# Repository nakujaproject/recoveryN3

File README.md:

# recoveryN3
Everything pertaining recovery system for N3 Rocket 2023

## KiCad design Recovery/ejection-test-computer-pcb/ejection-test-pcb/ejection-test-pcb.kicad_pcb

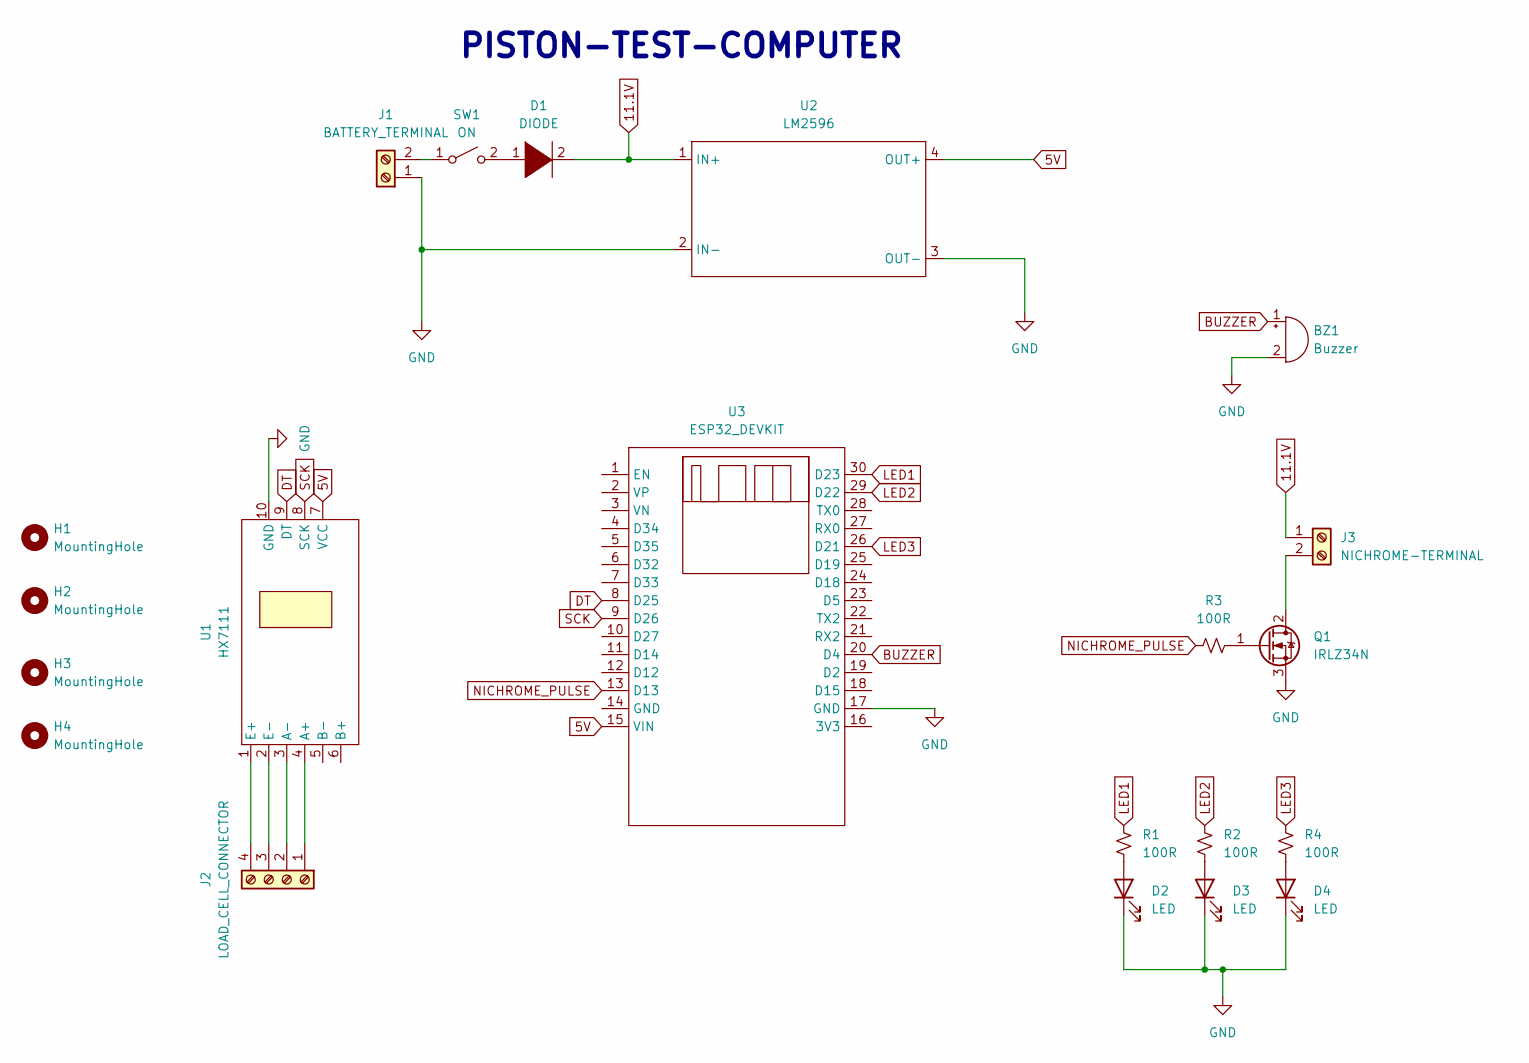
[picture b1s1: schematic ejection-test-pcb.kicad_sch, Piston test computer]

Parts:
BZ1: Buzzer; BUZZER
D1: DIODE; D_DO-35_SOD27_P10.16mm_Horizontal
D2, D3, D4: LED; LED_D5.0mm
H1, H2, H3, H4: MountingHole; MountingHole_3.2mm_M3
J1: BATTERY_TERMINAL; TerminalBlock_bornier-2_P5.08mm
J2: LOAD_CELL_CONNECTOR; TerminalBlock_bornier-4_P5.08mm
J3: NICHROME-TERMINAL; TerminalBlock_bornier-2_P5.08mm
Q1: IRLZ34N; TO-220-3_Vertical
R1, R2, R3, R4: 100R; R_Axial_DIN0207_L6.3mm_D2.5mm_P10.16mm_Horizontal
SW1: ON; KDC1-11-ROCKER-SWITCH
U1: HX7111; HX711
U2: LM2596; LM2596-BUCK-CONVERTER
U3: ESP32_DEVKIT

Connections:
5V: U1.7 (VCC), U2.4 (OUT+), U3.15 (VIN)
11.1V: D1.2 (A), J3.1, U2.1 (IN+)
BUZZER: BZ1.1 (-), U3.20 (D4)
DT: U1.9 (DT), U3.8 (D25)
GND: BZ1.2 (+), D2.1 (K), D3.1 (K), D4.1 (K), J1.1, Q1.3 (S), U1.10 (GND), U2.2 (IN-), U2.3 (OUT-), U3.17 (GND)
LED1: R1.1, U3.18 (D15), U3.30 (D23)
LED2: R2.1, U3.29 (D22)
LED3: R4.1, U3.26 (D21)
NICHROME_PULSE: R3.2, U3.13 (D13)
unnamed: D1.1 (K), SW1.2 (B)
unnamed: D2.2 (A), R1.2
unnamed: D3.2 (A), R2.2
unnamed: D4.2 (A), R4.2
unnamed: J1.2, SW1.1 (A)
unnamed: J2.1, U1.4 (A+)
unnamed: J2.2, U1.3 (A-)
unnamed: J2.3, U1.2 (E-)
unnamed: J2.4, U1.1 (E+)
unnamed: J3.2, Q1.2 (D)
unnamed: Q1.1 (G), R3.1
SCK: U1.8 (SCK), U3.9 (D26)

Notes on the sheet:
PISTON-TEST-COMPUTER

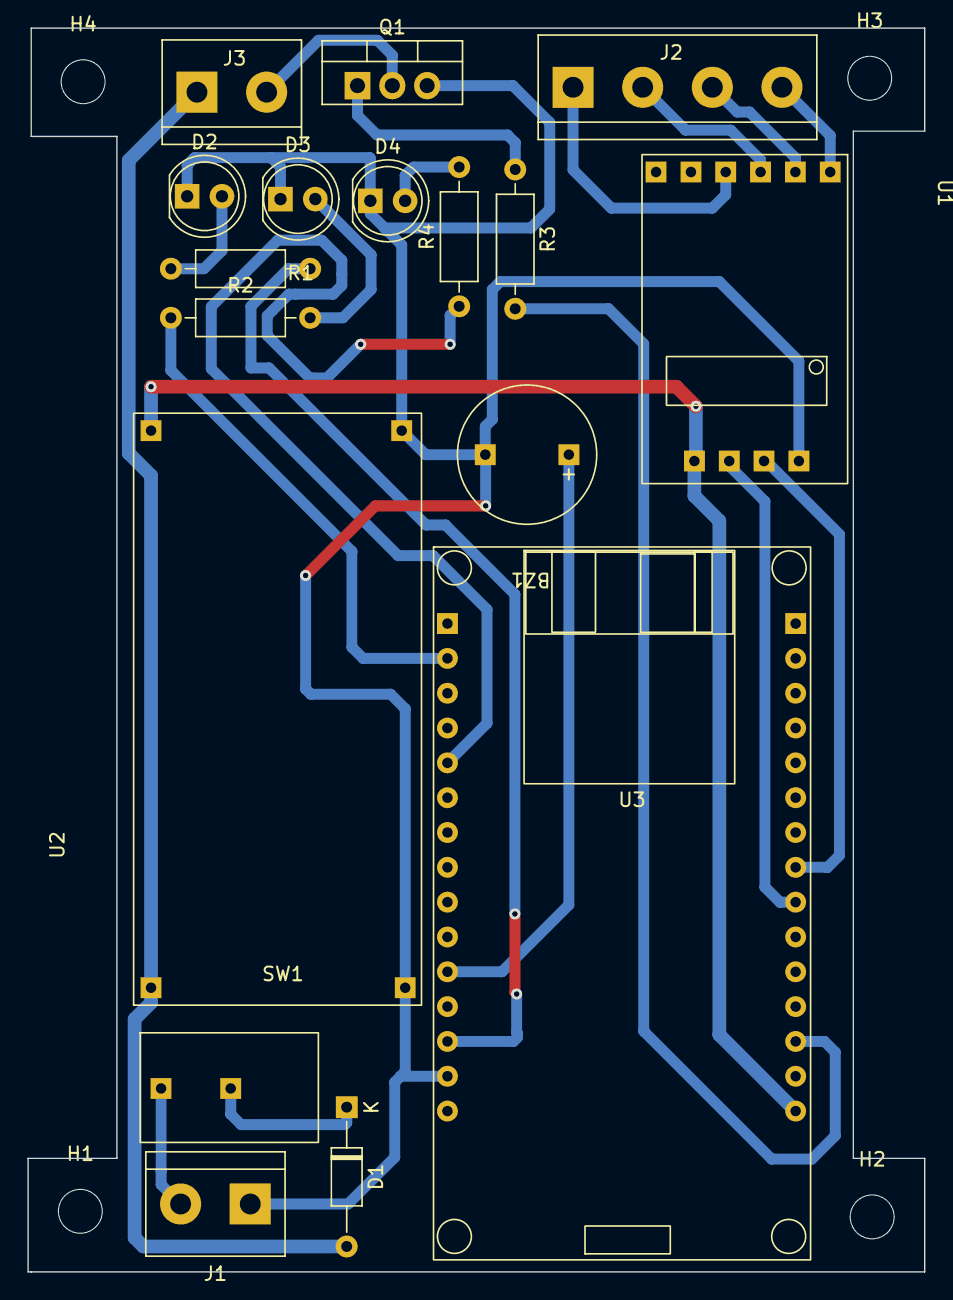
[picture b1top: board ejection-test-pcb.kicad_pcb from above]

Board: 2 copper layers, 65.4 x 90.7 mm, 21 parts (0 on the bottom side), 21 nets.

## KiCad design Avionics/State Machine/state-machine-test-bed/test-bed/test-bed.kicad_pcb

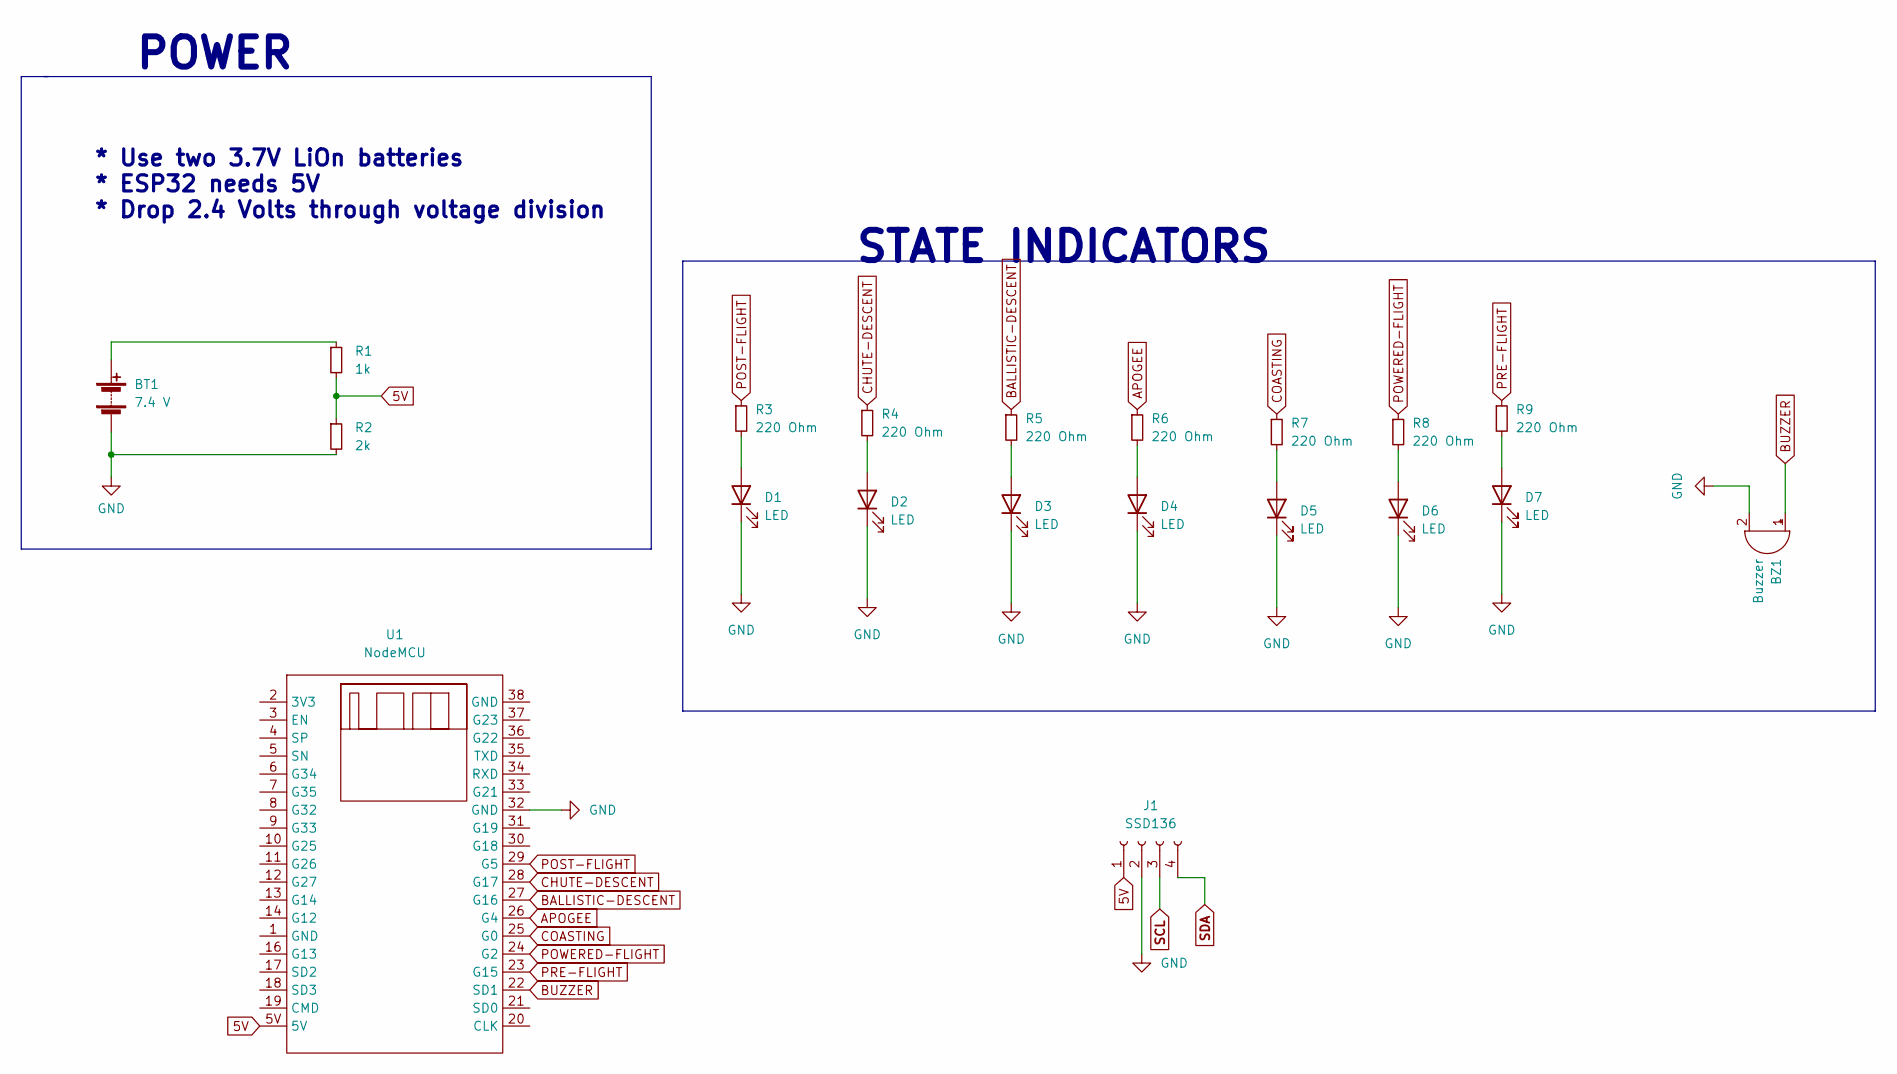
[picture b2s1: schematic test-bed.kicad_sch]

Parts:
BT1: 7.4 V; TerminalBlock_Altech_AK300-2_P5.00mm
BZ1: Buzzer; JST_EH_B2B-EH-A_1x02_P2.50mm_Vertical
D1, D2, D3, D4, D5, D6, D7: LED; LED_D3.0mm
J1: SSD136; PinHeader_1x04_P2.54mm_Vertical
R1: 1k; R_Axial_DIN0207_L6.3mm_D2.5mm_P10.16mm_Horizontal
R2: 2k; R_Axial_DIN0207_L6.3mm_D2.5mm_P10.16mm_Horizontal
R3, R4, R5, R6, R7, R8, R9: 220 Ohm; R_Axial_DIN0207_L6.3mm_D2.5mm_P10.16mm_Horizontal
U1: NodeMCU; NODEMCU

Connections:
5V: J1.1, R1.2, R2.1, U1.5V
APOGEE: R6.1, U1.26 (G4)
BALLISTIC-DESCENT: R5.1, U1.27 (G16)
BUZZER: BZ1.1 (-), U1.22 (SD1)
CHUTE-DESCENT: R4.1, U1.28 (G17)
COASTING: R7.1, U1.25 (G0)
GND: BT1.2 (-), BZ1.2 (+), D1.1 (K), D2.1 (K), D3.1 (K), D4.1 (K), D5.1 (K), D6.1 (K), D7.1 (K), J1.2, R2.2, U1.32 (GND)
unnamed: BT1.1 (+), R1.1
unnamed: D1.2 (A), R3.2
unnamed: D2.2 (A), R4.2
unnamed: D3.2 (A), R5.2
unnamed: D4.2 (A), R6.2
unnamed: D5.2 (A), R7.2
unnamed: D6.2 (A), R8.2
unnamed: D7.2 (A), R9.2
POST-FLIGHT: R3.1, U1.29 (G5)
POWERED-FLIGHT: R8.1, U1.24 (G2)
PRE-FLIGHT: R9.1, U1.23 (G15)
SCL: J1.3
SDA: J1.4

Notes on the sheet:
STATE INDICATORS
* Use two 3.7V LiOn batteries * ESP32 needs 5V * Drop 2.4 Volts through voltage division
POWER

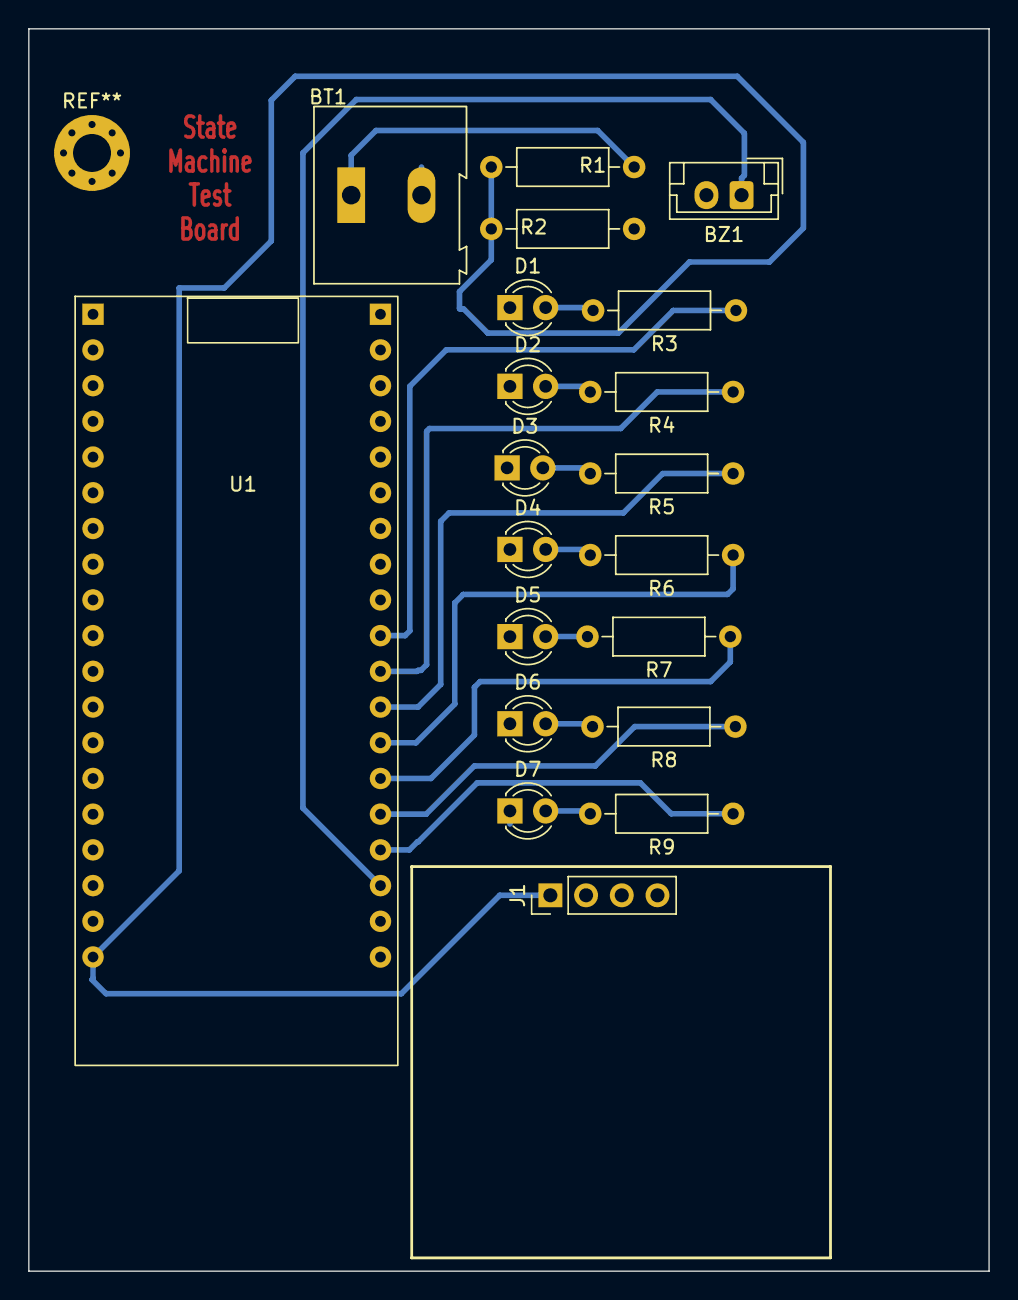
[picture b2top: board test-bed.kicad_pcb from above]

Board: 2 copper layers, 68.3 x 88.4 mm, 20 parts (0 on the bottom side), 18 nets.

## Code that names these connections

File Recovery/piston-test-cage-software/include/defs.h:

/* debug parameters for use during testing - disable before launch */
#define DEBUG 1

#if DEBUG == 1

#define debug(x) Serial.print(x)
#define debugln(x) Serial.println(x)
#define debugf(x, y) Serial.printf(x, y)

#else

#define debug(x)
#define debugln(x)
#define debugf(x, y)

#endif

#define CALLIBRATION_FACTOR 100

const char* SSID = "Galaxy";
const char* PASSWORD = "luwa2131";

const char* MQTT_BROKER = "192.168.208.19";
uint16_t MQTT_PORT = 1883;

// pinouts
const int buzzer = 4;
const int nichrome = 32;
const int led1 = 23;
const int led2 = 22;
const int led3 = 21;
const int load_cell_dt = 27;
const int load_cell_sck = 26;

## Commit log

2023-01-16 created initial docs
2023-01-17 added download links
2023-01-17 added schematic design for flight-computer test bed
2023-01-18 fixes issue #3: communication system research
2023-01-18 finished routing for state-machine test board
2023-01-18 fixes issue #3 Flight data logging with SD card
2023-01-18 fixes issue #4 Flight data logging with SD card
2023-01-18 fixes issue #3:communication system research
2023-01-23 Create Recovery
    Contains all research and designs pertaining Recovery subystem
2023-01-23 Recovery subystem
2023-01-25 added STEP files for ejection mechanism
2023-01-30 Closes issue #4 Flight data logging with SD card
2023-01-30 changed igniter pin to pin 18 that remains low on boot
2023-01-30 closes issue #22: created a document for pyro-bolts manufacturing process
2023-01-30 closes issue #22: pyrotechnic bolt design document
2023-01-31 added freeRTOS code to test firing circuit
2023-01-31 changed firing pin delay time to prevent queue blocking
2023-02-03 Recovery Team Work
2023-02-14 contributes to issue #6
2023-02-22 added BOM for building a custom piston
2023-02-22 added crimson powder preparation modes
2023-02-22 added initial template for ejection testing app
2023-02-22 added class method to search for serial ports
2023-03-08 added ejection test videos
2023-03-20 Power Distribution Board
2023-03-20 Added PDB Schematic PDF
2023-03-20 Wrap Around Patch Antenna
2023-03-20 4 element patch design
2023-03-27 Add files via upload
    Schematic for the New N3 Power Distribution Board.
2023-04-12 added RSSI antenna test results
2023-04-12 added flight computer 3d designs
2023-04-12 added load cell callibration function
2023-04-13 added piston test system flowchart
2023-04-14 added transmit function
2023-04-15 added websocket
2023-04-15 added test pcb
2023-04-18 added paho-mqtt-client for test app
2023-04-19 improved UI
2023-04-27 updated nichrome counter time
2023-04-27 added nichrome counter time
2023-05-20 piston test web UI
2023-05-24 add loging script and update UI
2023-05-26 add data count to transmitted data
2023-06-01 added 3d printed stl files rod and nut
2023-06-01 3D printed models bolt nut
2023-07-04 THe latest pdb
2023-07-04 Latest PDB
